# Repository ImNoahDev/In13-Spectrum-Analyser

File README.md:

# Nixie tube spectrum analyser

Warning: this is currently untested

I have designed an audio spectrum analyser that breaks an audio signal down into 7 frequency bands and displays each band on an in13 nixie tube. My project has Wifi allowing for smart home control. My project has a volume (changes sensitivity) and a brightness potentiometer. Each PCB takes a single audio signal input and 2 can be used for full stereo.

The case uses a laser cut kerf bend to allow the wrap around sheet to be cut in a single part. 

## Assembly instructions.

First manufacture and assemble the PCB according to the KiCad files. Next 3d print the top and bottom parts of the case. place the PCB onto the standoffs of the case with layer B (with the least components) facing upwards. Place the top of the case on and screw all part onto the standoffs. Laser cut the Wrap around and screw it in to the bottom mounting holes of the case while wrapping around the case to give a wooden front finish.

Code can be flashed through the USB port due to the built in USB-Serial converter.

## BOM

Note this is for 2x units (Left and Right) because most PCB manufacturers require at least 2 assembled and the price is not significantly more for 2 vs 1. This allows one per audio channel. The price of the tubes also wildly swings so I have put a placeholder value in that is roughly correct (depending on where you get them).

| Part name         | Cost    | Use                 | URL       |
| ----------------- | ------- | ------------------- | --------- |
| PCB Manufacture   | $11.20  | PCB                 | jlpcb.com |
| Economic PCBA     | $66.22  | Assemble PCB        | jlpcb.com |
| Components (PCBA) | $61.93  | Components for PCBA | jlpcb.com |
| Shipping          | $15     | PCB shipping        | jlpcb.com |
| In13 tubes        | $200    | Tubes               | Ebay      |
| Total:            | $343.35 |                     |           |

| Comment                     | Designator | Footprint                                  | Quantity |
| --------------------------- | ---------- | ------------------------------------------ | -------- |
| MJE340_                     | Q4         | TO126                                      | 1        |
| 10uF                        | C22        | C_1206_3216Metric                          | 1        |
| 4.7k                        | R38        | R_0603_1608Metric                          | 1        |
| 15k 1W                      | R14        | R_2512_6332Metric                          | 1        |
| 820k 0.25w 200v             | R44        | R_1206_3216Metric                          | 1        |
| 820 1/4w                    | R22        | R_1206_3216Metric                          | 1        |
| 0.1uF                       | C28        | C_0201_0603Metric                          | 1        |
| 10v 22uF                    | C5         | C_1206_3216Metric                          | 1        |
| 10uF                        | C11        | C_1206_3216Metric                          | 1        |
| 15k 1W                      | R34        | R_2512_6332Metric                          | 1        |
| USB_C_Receptacle_USB2.0_14P | J1         | USB_C_Receptacle_HCTL_HC-TYPE-C-16P-01A    | 1        |
| SW_Push                     | SW2        | 4312560387X6                               | 1        |
| MJE340_                     | Q2         | TO126                                      | 1        |
| 4.7k                        | R8         | R_0603_1608Metric                          | 1        |
| 0.05 1w                     | R43        | R_2512_6332Metric                          | 1        |
| 0.1uF                       | C15        | C_0603_1608Metric                          | 1        |
| ESP32-WROOM-32              | U3         | ESP32-WROOM-32                             | 1        |
| 15k 1W                      | R19        | R_2512_6332Metric                          | 1        |
| 2.2k 1/4W                   | R26        | R_1206_3216Metric                          | 1        |
| 0.1uF                       | C27        | C_0201_0603Metric                          | 1        |
| 0.1uF                       | C13        | C_0603_1608Metric                          | 1        |
| 2.2k 1/4W                   | R16        | R_1206_3216Metric                          | 1        |
| 2.2k 1/4W                   | R36        | R_1206_3216Metric                          | 1        |
| 10k                         | RV2        | Potentiometer_Alps_RK09K_Single_Horizontal | 1        |
| MSGEQ7                      | U2         | DIP-8_W7.62mm                              | 1        |
| 0.1uf                       | C25        | C_0201_0603Metric                          | 1        |
| SW_Push                     | SW3        | SW_SPST_SKQG_WithStem                      | 1        |
| 4.7k                        | R33        | R_0603_1608Metric                          | 1        |
| 820 1/4w                    | R37        | R_1206_3216Metric                          | 1        |
| MCP6002-xMC                 | U5         | DFN-8-1EP_3x2mm_P0.5mm_EP1.75x1.45mm       | 1        |
| 2.2k 1/4W                   | R31        | R_1206_3216Metric                          | 1        |
| IRFP250N                    | Q8         | TO-247-3_Horizontal_TabDown                | 1        |
| 56 uH                       | L1         | L_Ferrocore_DLG-0403                       | 1        |
| 10k                         | R46        | R_0603_1608Metric                          | 1        |
| 200K                        | R3         | R_0402_1005Metric                          | 1        |
| 4.7k                        | R18        | R_0603_1608Metric                          | 1        |
| 820 1/4w                    | R27        | R_1206_3216Metric                          | 1        |
| MJE340_                     | Q1         | TO126                                      | 1        |
| 0.1uF 10v                   | C10        | C_0402_1005Metric                          | 1        |
| 4.7k                        | R23        | R_0603_1608Metric                          | 1        |
| MJE340_                     | Q6         | TO126                                      | 1        |
| 4.7uF 10v                   | C1         | C_1206_3216Metric                          | 1        |
| 15k 1W                      | R24        | R_2512_6332Metric                          | 1        |
| 10K                         | R7         | R_0603_1608Metric                          | 1        |
| MJE340_                     | Q3         | TO126                                      | 1        |
| 0.1uF                       | C14        | C_0603_1608Metric                          | 1        |
| 0.1uF                       | C19        | C_0603_1608Metric                          | 1        |
| 0.1uF                       | C26        | C_0201_0603Metric                          | 1        |
| 100uF 16v                   | C21        | C_1206_3216Metric                          | 1        |
| 10V 1uF                     | C7         | C_1206_3216Metric                          | 1        |
| 10V 0.1uF                   | C4         | C_0402_1005Metric                          | 1        |
| MCP6002-xMC                 | U4         | DFN-8-1EP_3x2mm_P0.5mm_EP1.75x1.45mm       | 1        |
| 0.1uF                       | C17        | C_0603_1608Metric                          | 1        |
| 470k 1/4w                   | R40        | R_1206_3216Metric                          | 1        |
| 820 1/4w                    | R42        | R_1206_3216Metric                          | 1        |
| 0.1uF                       | C16        | C_0603_1608Metric                          | 1        |
| 10k 0.25w 200v              | R45        | R_1206_3216Metric                          | 1        |
| 15k 1W                      | R10        | R_2512_6332Metric                          | 1        |
| 470k 1/4w                   | R20        | R_1206_3216Metric                          | 1        |
| 47uF 200V                   | C23        | CP_Radial_D13.0mm_P5.00mm                  | 1        |
| SW_Push                     | SW1        | SW_SPST_SKQG_WithStem                      | 1        |
| RXD                         | TP2        | TestPoint_Pad_D1.0mm                       | 1        |
| 10K                         | R4         | R_0603_1608Metric                          | 1        |
| 5.1K                        | R1         | R_0402_1005Metric                          | 1        |
| 470k 1/4w                   | R25        | R_1206_3216Metric                          | 1        |
| 820 1/4w                    | R17        | R_1206_3216Metric                          | 1        |
| 470k 1/4w                   | R30        | R_1206_3216Metric                          | 1        |
| 10V 0.1uF                   | C6         | C_0402_1005Metric                          | 1        |
| 5.1K                        | R2         | R_0402_1005Metric                          | 1        |
| 470k 1/4w                   | R15        | R_1206_3216Metric                          | 1        |
| 0.1uF 10v                   | C9         | C_0402_1005Metric                          | 1        |
| 4.7k                        | R13        | R_0603_1608Metric                          | 1        |
| 10k                         | R47        | R_0603_1608Metric                          | 1        |
| TXD                         | TP1        | TestPoint_Pad_D1.0mm                       | 1        |
| 820 1/4w                    | R12        | R_1206_3216Metric                          | 1        |
| 4.7k                        | R28        | R_0603_1608Metric                          | 1        |
| 470k 1/4w                   | R9         | R_1206_3216Metric                          | 1        |
| 10k                         | RV3        | Potentiometer_Alps_RK09K_Single_Horizontal | 1        |
| MAX1771xSA                  | U11        | SO-8_3.9x4.9mm_P1.27mm                     | 1        |
| 2.2k 1/4W                   | R21        | R_1206_3216Metric                          | 1        |
| 18K                         | R5         | R_0603_1608Metric                          | 1        |
| 33k                         | R6         | R_0603_1608Metric                          | 1        |
| CH340C                      | U7         | SOIC-16_3.9x9.9mm_P1.27mm                  | 1        |
| MJE340_                     | Q5         | TO126                                      | 1        |
| UF4004                      | D2         | DIOAD1055W87L533D272                       | 1        |
| 0.1uF                       | C18        | C_0603_1608Metric                          | 1        |
| 10V 3.3uF                   | C3         | C_1206_3216Metric                          | 1        |
| 2.2k 1/4W                   | R41        | R_1206_3216Metric                          | 1        |
| 0.1uF                       | C12        | C_0603_1608Metric                          | 1        |
| 470k 1/4w                   | R35        | R_1206_3216Metric                          | 1        |
| MCP6002-xMC                 | U6         | DFN-8-1EP_3x2mm_P0.5mm_EP1.75x1.45mm       | 1        |
| 15k 1W                      | R39        | R_2512_6332Metric                          | 1        |
| AMS1117-3.3                 | U1         | SOT-223-3_TabPin2                          | 1        |
| 0.1uF 10v                   | C2         | C_0402_1005Metric                          | 1        |
| 15k 1W                      | R29        | R_2512_6332Metric                          | 1        |
| Conn_Coaxial                | J3         | RCA-Phono_CUI-Devices_RCJ-01X_Horizontal   | 1        |
| 0.1uF                       | C20        | C_0603_1608Metric                          | 1        |
| 33pF                        | C8         | C_0402_1005Metric                          | 1        |
| 0.1uF                       | C29        | C_0201_0603Metric                          | 1        |
| MJE340_                     | Q7         | TO126                                      | 1        |
| 0.1uF 250v                  | C24        | C_1206_3216Metric                          | 1        |
| 820 1/4w                    | R32        | R_1206_3216Metric                          | 1        |
| MCP6002-xMC                 | U18        | DFN-8-1EP_3x2mm_P0.5mm_EP1.75x1.45mm       | 1        |
| 2.2k 1/4W                   | R11        | R_1206_3216Metric                          | 1        |

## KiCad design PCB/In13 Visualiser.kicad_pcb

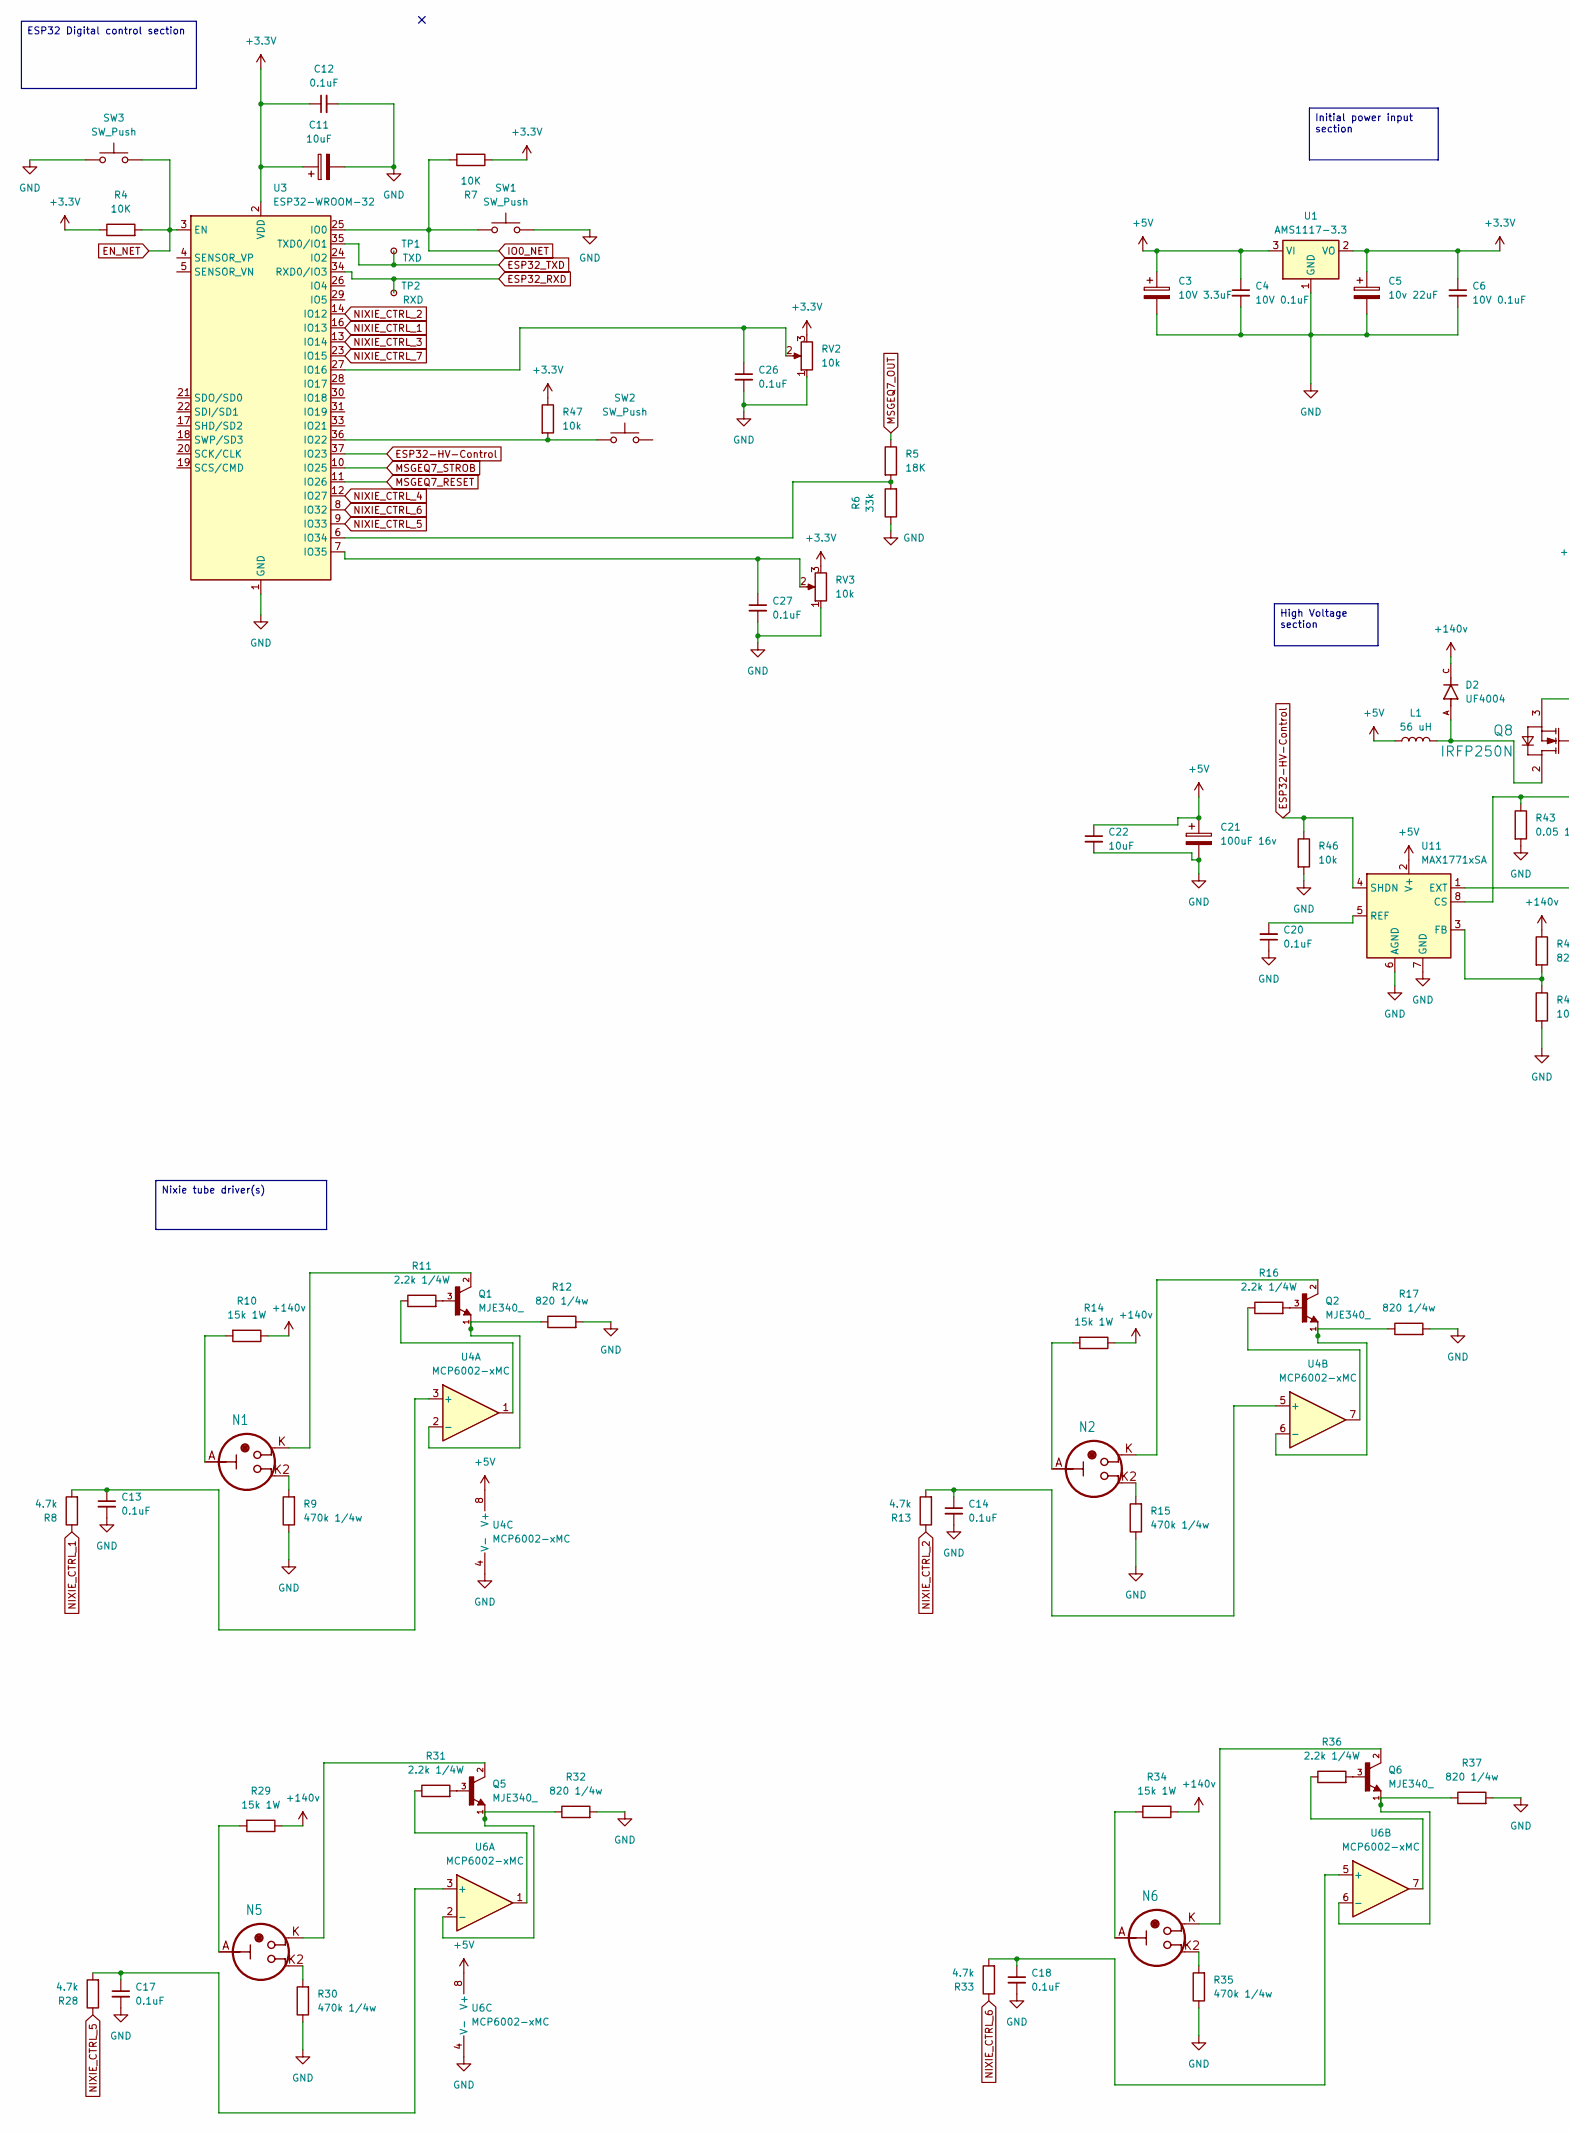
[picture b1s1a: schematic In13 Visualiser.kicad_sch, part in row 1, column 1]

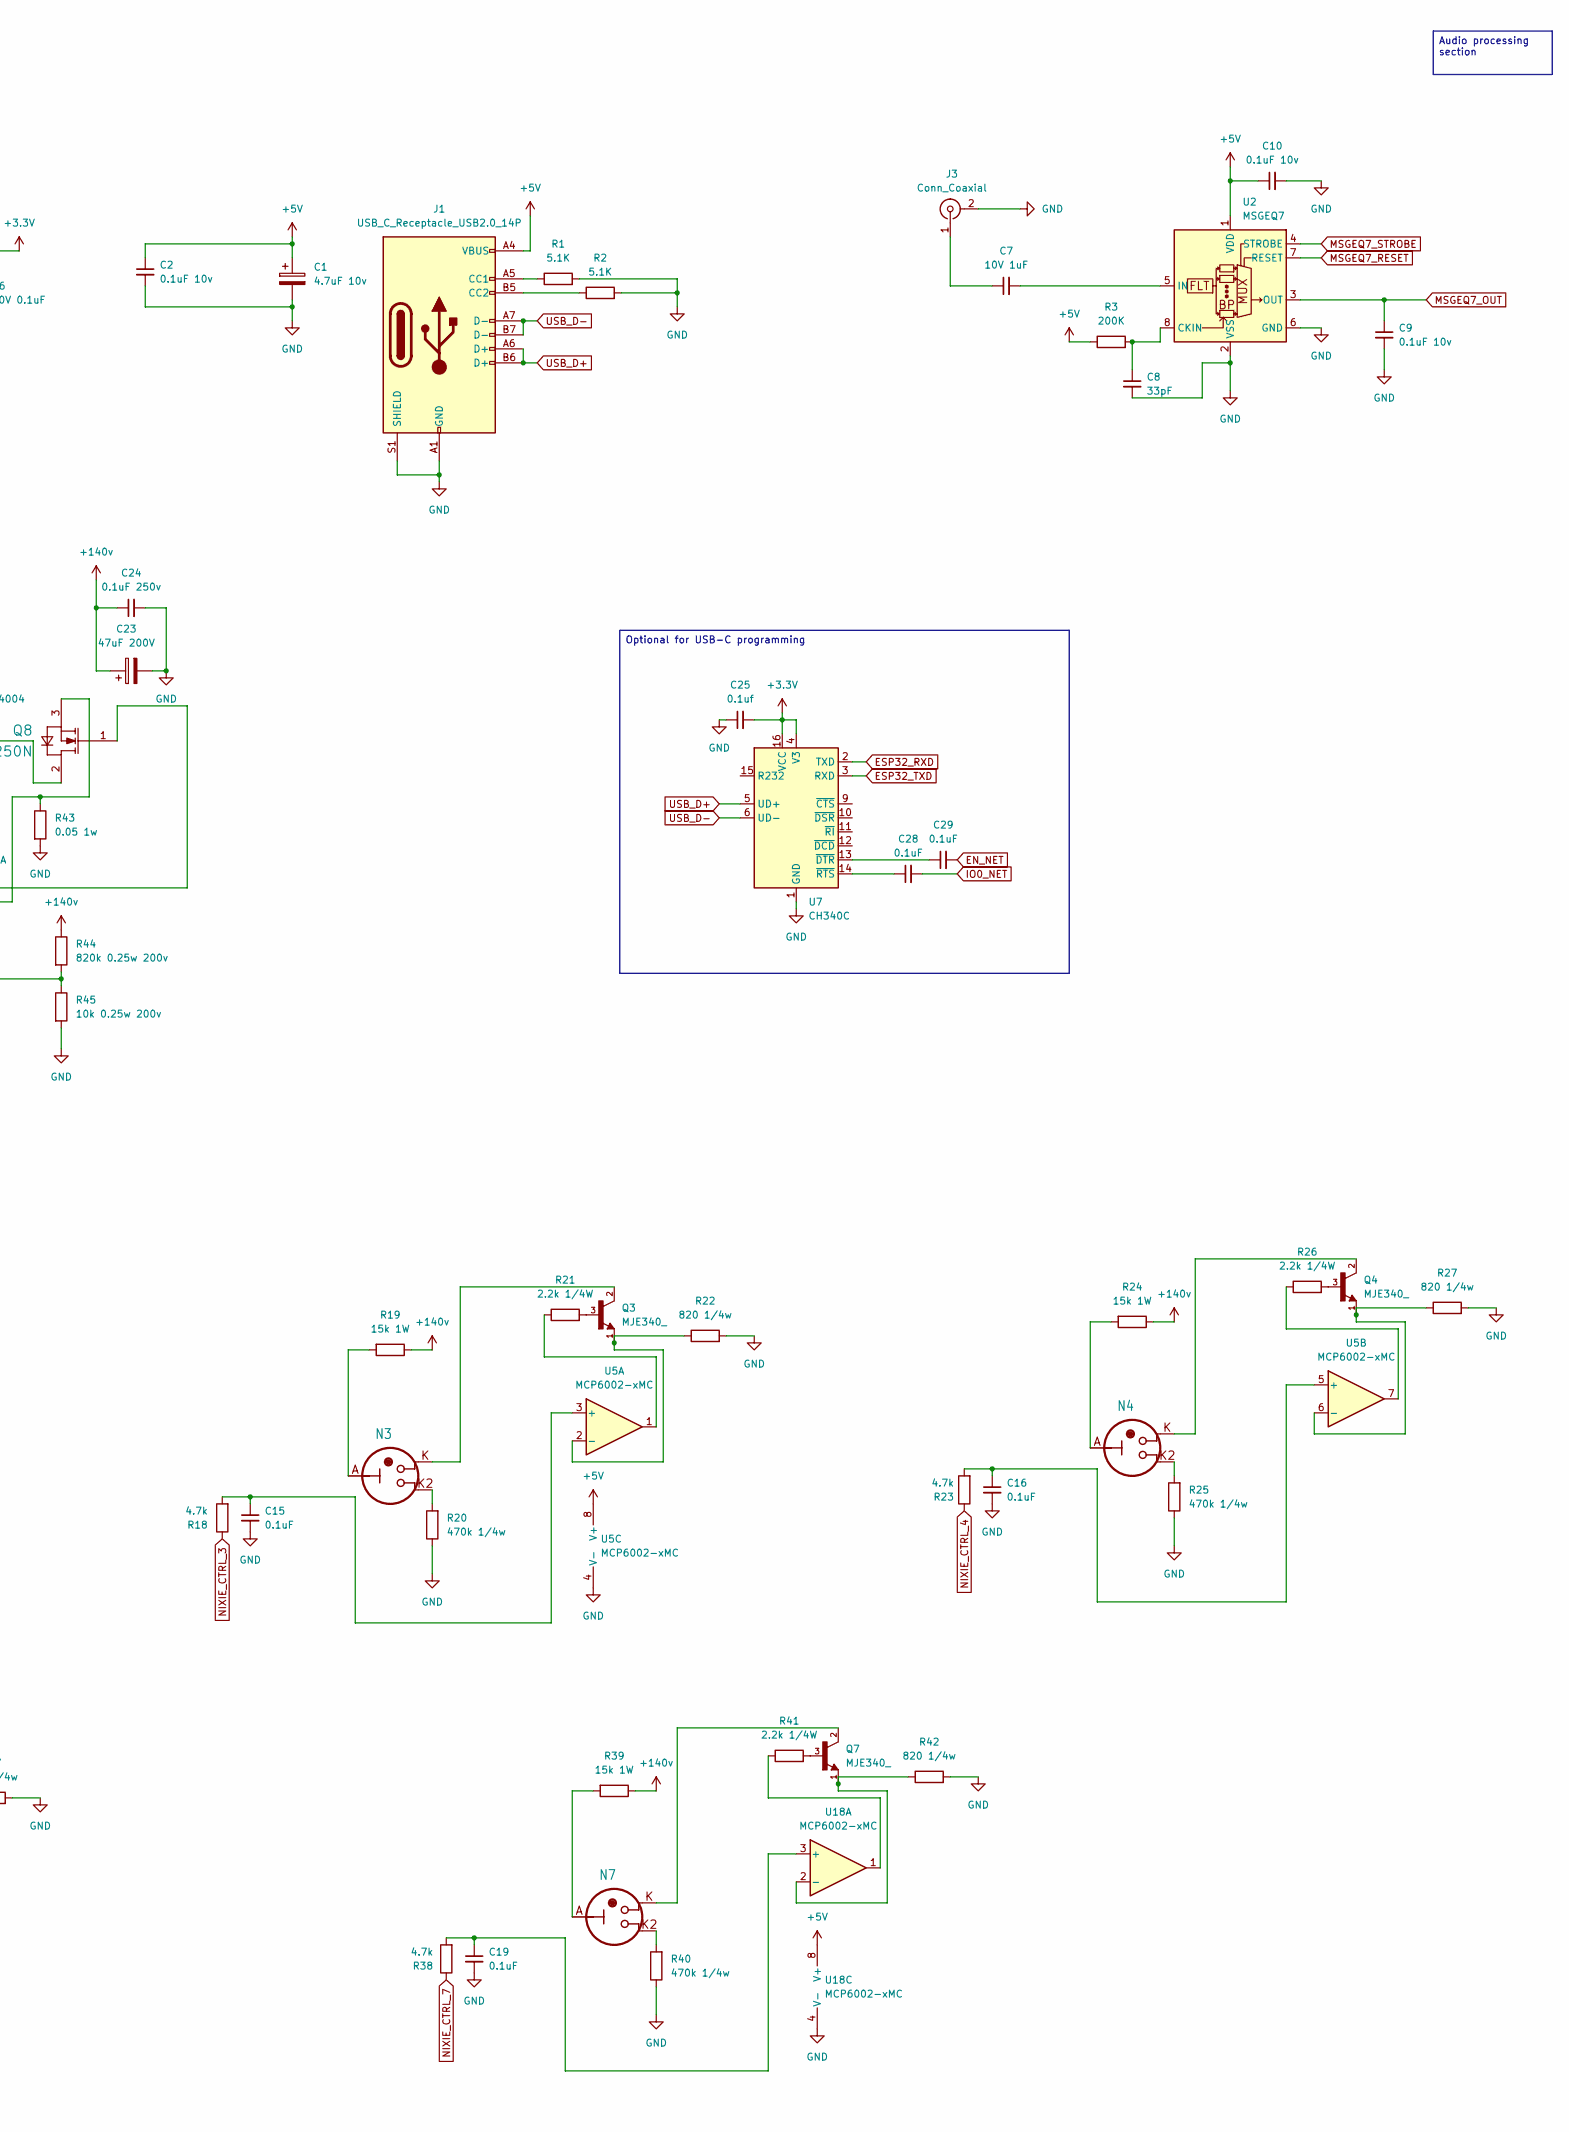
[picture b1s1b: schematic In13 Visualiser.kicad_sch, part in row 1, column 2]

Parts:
C1: 4.7uF 10v; C_1206_3216Metric
C2, C9, C10: 0.1uF 10v; C_0402_1005Metric
C3: 10V 3.3uF; C_1206_3216Metric
C4, C6: 10V 0.1uF; C_0402_1005Metric
C5: 10v 22uF; C_1206_3216Metric
C7: 10V 1uF; C_1206_3216Metric
C8: 33pF; C_0402_1005Metric
C11, C22: 10uF; C_1206_3216Metric
C12, C13, C14, C15, C16, C17, C18, C19, C20: 0.1uF; C_0603_1608Metric
C21: 100uF 16v; C_1206_3216Metric
C23: 47uF 200V; CP_Radial_D13.0mm_P5.00mm
C24: 0.1uF 250v; C_1206_3216Metric
C25: 0.1uf; C_0201_0603Metric
C26, C27, C28, C29: 0.1uF; C_0201_0603Metric
D2: UF4004; DIOAD1055W87L533D272; PARTREV N/A
J1: USB_C_Receptacle_USB2.0_14P; USB_C_Receptacle_HCTL_HC-TYPE-C-16P-01A
J3: Conn_Coaxial; RCA-Phono_CUI-Devices_RCJ-01X_Horizontal
L1: 56 uH; L_Ferrocore_DLG-0403
N1, N2, N3, N4, N5, N6, N7: nixies-us-IN-13
Q1, Q2, Q3, Q4, Q5, Q6, Q7: MJE340_; TO126
Q8: IRFP250N; TO-247-3_Horizontal_TabDown
R1, R2: 5.1K; R_0402_1005Metric
R3: 200K; R_0402_1005Metric
R4, R7: 10K; R_0603_1608Metric
R5: 18K; R_0603_1608Metric
R6: 33k; R_0603_1608Metric
R8, R13, R18, R23, R28, R33, R38: 4.7k; R_0603_1608Metric
R9, R15, R20, R25, R30, R35, R40: 470k 1/4w; R_1206_3216Metric
R10, R14, R19, R24, R29, R34, R39: 15k 1W; R_2512_6332Metric
R11, R16, R21, R26, R31, R36, R41: 2.2k 1/4W; R_1206_3216Metric
R12, R17, R22, R27, R32, R37, R42: 820 1/4w; R_1206_3216Metric
R43: 0.05 1w; R_2512_6332Metric
R44: 820k 0.25w 200v; R_1206_3216Metric
R45: 10k 0.25w 200v; R_1206_3216Metric
R46, R47: 10k; R_0603_1608Metric
RV2, RV3: 10k; Potentiometer_Alps_RK09K_Single_Horizontal
SW1, SW3: SW_Push; SW_SPST_SKQG_WithStem
SW2: SW_Push; 4312560387X6
TP1: TXD; TestPoint_Pad_D1.0mm
TP2: RXD; TestPoint_Pad_D1.0mm
U1: AMS1117-3.3; SOT-223-3_TabPin2
U2: MSGEQ7; DIP-8_W7.62mm
U3: ESP32-WROOM-32
U4, U5, U6, U18: MCP6002-xMC; DFN-8-1EP_3x2mm_P0.5mm_EP1.75x1.45mm
U7: CH340C; SOIC-16_3.9x9.9mm_P1.27mm
U11: MAX1771xSA; SO-8_3.9x4.9mm_P1.27mm

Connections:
+3.3V: C5.1, C6.1, C11.1, C12.1, C25.2, R4.1, R7.1, R47.1, RV2.3, RV3.3, U1.2 (VO), U3.2 (VDD), U7.4 (V3), U7.16 (VCC)
+5V: C1.1, C2.1, C3.1, C4.1, C10.1, C21.1, C22.1, J1.A4 (VBUS), J1.A9 (VBUS), J1.B4 (VBUS), J1.B9 (VBUS), L1.1, R3.1, U1.3 (VI), U2.1 (VDD), U4.8 (V+), U5.8 (V+), U6.8 (V+), U11.2 (V+), U18.8 (V+)
+140v: C23.1, C24.1, D2.C, R10.1, R14.1, R19.1, R24.1, R29.1, R34.1, R39.1, R44.1
EN_NET: C29.2, R4.2, SW3.2, U3.3 (EN)
ESP32-HV-Control: R46.1, U3.37 (IO23), U11.4 (SHDN)
ESP32_RXD: TP2.1, U3.34 (RXD0/IO3), U7.2 (TXD)
ESP32_TXD: TP1.1, U3.35 (TXD0/IO1), U7.3 (RXD)
GND: C1.2, C2.2, C3.2, C4.2, C5.2, C6.2, C8.2, C9.2, C10.2, C11.2, C12.2, C13.2, C14.2, C15.2, C16.2, C17.2, C18.2, C19.2, C20.1, C21.2, C22.2, C23.2, C24.2, C25.1, C26.2, C27.2, J1.A1 (GND), J1.A12 (GND), J1.B1 (GND), J1.B12 (GND), J1.S1 (SHIELD), J3.2 (Ext), R1.2, R2.2, R6.1, R9.1, R12.2, R15.1, R17.2, R20.1, R22.2, R25.1, R27.2, R30.1, R32.2, R35.1, R37.2, R40.1, R42.2, R43.2, R45.2, R46.2, RV2.1, RV3.1, SW1.2, SW3.1, U1.1 (GND), U2.2 (VSS), U2.6 (GND), U3.1 (GND), U3.15 (GND), U3.38 (GND), U3.39 (GND), U4.4 (V-), U4.9 (V-), U5.4 (V-), U5.9 (V-), U6.4 (V-), U6.9 (V-), U7.1 (GND), U11.6 (AGND), U11.7 (GND), U18.4 (V-), U18.9 (V-)
IO0_NET: C28.2, R7.2, SW1.1, U3.25 (IO0)
MSGEQ7_OUT: C9.1, R5.1, U2.3 (OUT)
MSGEQ7_RESET: U2.7 (RESET), U3.11 (IO26)
MSGEQ7_STROB: U3.10 (IO25)
MSGEQ7_STROBE: U2.4 (STROBE)
NIXIE_CTRL_1: R8.1, U3.16 (IO13)
NIXIE_CTRL_2: R13.1, U3.14 (IO12)
NIXIE_CTRL_3: R18.1, U3.13 (IO14)
NIXIE_CTRL_4: R23.1, U3.12 (IO27)
NIXIE_CTRL_5: R28.1, U3.9 (IO33)
NIXIE_CTRL_6: R33.1, U3.8 (IO32)
NIXIE_CTRL_7: R38.1, U3.23 (IO15)
unnamed: J1.A5 (CC1), R1.1
unnamed: J1.B5 (CC2), R2.1
unnamed: C7.1, J3.1 (In)
unnamed: N1.A, R10.2
unnamed: N1.K2, R9.2
unnamed: N1.K, Q1.2
unnamed: N2.A, R14.2
unnamed: N2.K2, R15.2
unnamed: N2.K, Q2.2
unnamed: N3.A, R19.2
unnamed: N3.K2, R20.2
unnamed: N3.K, Q3.2
unnamed: N4.A, R24.2
unnamed: N4.K2, R25.2
unnamed: N4.K, Q4.2
unnamed: N5.A, R29.2
unnamed: N5.K2, R30.2
unnamed: N5.K, Q5.2
unnamed: N6.A, R34.2
unnamed: N6.K2, R35.2
unnamed: N6.K, Q6.2
unnamed: N7.A, R39.2
unnamed: N7.K2, R40.2
unnamed: N7.K, Q7.2
unnamed: Q1.3, R11.2
unnamed: Q2.3, R16.2
unnamed: Q3.3, R21.2
unnamed: Q4.3, R26.2
unnamed: Q5.3, R31.2
unnamed: Q6.3, R36.2
unnamed: Q7.3, R41.2
unnamed: D2.A, L1.2, Q8.2 (DRAIN)
unnamed: Q8.1 (GATE), U11.1 (EXT)
unnamed: Q8.3 (SOURCE), R43.1, U11.8 (CS)
unnamed: R11.1, U4.1
unnamed: R16.1, U4.7
unnamed: R21.1, U5.1
unnamed: R26.1, U5.7
unnamed: R31.1, U6.1
unnamed: R36.1, U6.7
unnamed: R41.1, U18.1
unnamed: C8.1, R3.2, U2.8 (CKIN)
unnamed: C7.2, U2.5 (IN)
unnamed: C26.1, RV2.2, U3.27 (IO16)
unnamed: R47.2, SW2.1, U3.36 (IO22)
unnamed: R5.2, R6.2, U3.6 (IO34)
unnamed: C27.1, RV3.2, U3.7 (IO35)
unnamed: C13.1, R8.2, U4.3 (+)
unnamed: Q1.1, R12.1, U4.2 (-)
unnamed: C14.1, R13.2, U4.5 (+)
unnamed: Q2.1, R17.1, U4.6 (-)
unnamed: C15.1, R18.2, U5.3 (+)
unnamed: Q3.1, R22.1, U5.2 (-)
unnamed: C16.1, R23.2, U5.5 (+)
unnamed: Q4.1, R27.1, U5.6 (-)
unnamed: C17.1, R28.2, U6.3 (+)
unnamed: Q5.1, R32.1, U6.2 (-)
unnamed: C18.1, R33.2, U6.5 (+)
unnamed: Q6.1, R37.1, U6.6 (-)
unnamed: C29.1, U7.13 (~DTR)
unnamed: C28.1, U7.14 (~RTS)
unnamed: R44.2, R45.1, U11.3 (FB)
unnamed: C20.2, U11.5 (REF)
unnamed: C19.1, R38.2, U18.3 (+)
unnamed: Q7.1, R42.1, U18.2 (-)
USB_D+: J1.A6 (D+), J1.B6 (D+), U7.5 (UD+)
USB_D-: J1.A7 (D-), J1.B7 (D-), U7.6 (UD-)

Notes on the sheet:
Initial power input section
High Voltage section
Nixie tube driver(s)
ESP32 Digital control section
Audio processing section
Optional for USB-C programming

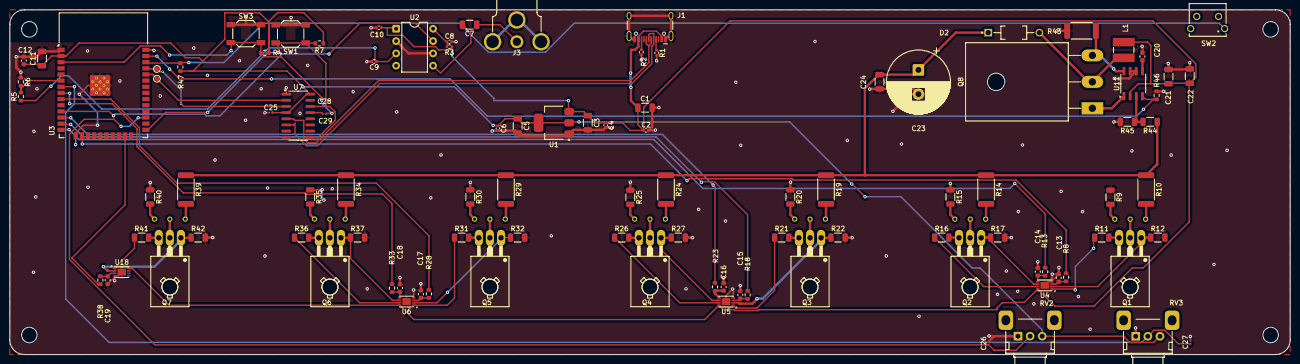
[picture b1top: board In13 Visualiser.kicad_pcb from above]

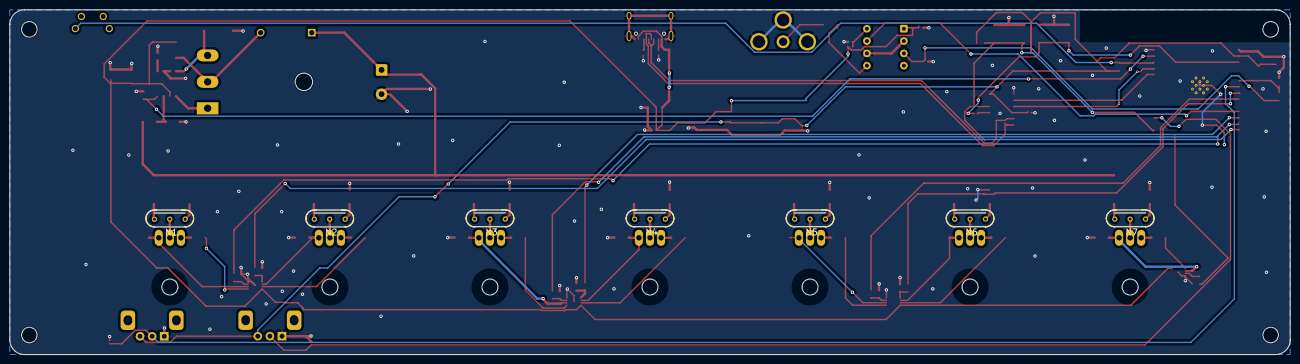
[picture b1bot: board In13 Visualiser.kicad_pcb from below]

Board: 2 copper layers, 264.2 x 71.1 mm, 115 parts (7 on the bottom side), 85 nets.

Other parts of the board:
Hole1, Hole2, Hole3, Hole4: MountingHole_3.2mm_M3

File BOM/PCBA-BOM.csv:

Comment,Designator,Footprint,LCSC,Quantity
MJE340_,Q4,TO126,,1
10uF,C22,C_1206_3216Metric,,1
4.7k,R38,R_0603_1608Metric,,1
15k 1W,R14,R_2512_6332Metric,,1
820k 0.25w 200v,R44,R_1206_3216Metric,,1
820 1/4w,R22,R_1206_3216Metric,,1
0.1uF,C28,C_0201_0603Metric,,1
10v 22uF,C5,C_1206_3216Metric,,1
10uF,C11,C_1206_3216Metric,,1
15k 1W,R34,R_2512_6332Metric,,1
USB_C_Receptacle_USB2.0_14P,J1,USB_C_Receptacle_HCTL_HC-TYPE-C-16P-01A,,1
SW_Push,SW2,4312560387X6,,1
MJE340_,Q2,TO126,,1
4.7k,R8,R_0603_1608Metric,,1
0.05 1w,R43,R_2512_6332Metric,,1
0.1uF,C15,C_0603_1608Metric,,1
ESP32-WROOM-32,U3,ESP32-WROOM-32,,1
15k 1W,R19,R_2512_6332Metric,,1
2.2k 1/4W,R26,R_1206_3216Metric,,1
0.1uF,C27,C_0201_0603Metric,,1
0.1uF,C13,C_0603_1608Metric,,1
2.2k 1/4W,R16,R_1206_3216Metric,,1
2.2k 1/4W,R36,R_1206_3216Metric,,1
10k,RV2,Potentiometer_Alps_RK09K_Single_Horizontal,,1
MSGEQ7,U2,DIP-8_W7.62mm,,1
0.1uf,C25,C_0201_0603Metric,,1
SW_Push,SW3,SW_SPST_SKQG_WithStem,,1
4.7k,R33,R_0603_1608Metric,,1
820 1/4w,R37,R_1206_3216Metric,,1
MCP6002-xMC,U5,DFN-8-1EP_3x2mm_P0.5mm_EP1.75x1.45mm,,1
2.2k 1/4W,R31,R_1206_3216Metric,,1
IRFP250N,Q8,TO-247-3_Horizontal_TabDown,,1
56 uH,L1,L_Ferrocore_DLG-0403,,1
10k,R46,R_0603_1608Metric,,1
200K,R3,R_0402_1005Metric,,1
4.7k,R18,R_0603_1608Metric,,1
820 1/4w,R27,R_1206_3216Metric,,1
MJE340_,Q1,TO126,,1
0.1uF 10v,C10,C_0402_1005Metric,,1
4.7k,R23,R_0603_1608Metric,,1
MJE340_,Q6,TO126,,1
4.7uF 10v,C1,C_1206_3216Metric,,1
15k 1W,R24,R_2512_6332Metric,,1
10K,R7,R_0603_1608Metric,,1
MJE340_,Q3,TO126,,1
0.1uF,C14,C_0603_1608Metric,,1
0.1uF,C19,C_0603_1608Metric,,1
0.1uF,C26,C_0201_0603Metric,,1
100uF 16v,C21,C_1206_3216Metric,,1
10V 1uF,C7,C_1206_3216Metric,,1
10V 0.1uF,C4,C_0402_1005Metric,,1
MCP6002-xMC,U4,DFN-8-1EP_3x2mm_P0.5mm_EP1.75x1.45mm,,1
0.1uF,C17,C_0603_1608Metric,,1
470k 1/4w,R40,R_1206_3216Metric,,1
820 1/4w,R42,R_1206_3216Metric,,1
0.1uF,C16,C_0603_1608Metric,,1
10k 0.25w 200v,R45,R_1206_3216Metric,,1
15k 1W,R10,R_2512_6332Metric,,1
470k 1/4w,R20,R_1206_3216Metric,,1
47uF 200V,C23,CP_Radial_D13.0mm_P5.00mm,,1
SW_Push,SW1,SW_SPST_SKQG_WithStem,,1
RXD,TP2,TestPoint_Pad_D1.0mm,,1
10K,R4,R_0603_1608Metric,,1
5.1K,R1,R_0402_1005Metric,,1
470k 1/4w,R25,R_1206_3216Metric,,1
820 1/4w,R17,R_1206_3216Metric,,1
470k 1/4w,R30,R_1206_3216Metric,,1
10V 0.1uF,C6,C_0402_1005Metric,,1
5.1K,R2,R_0402_1005Metric,,1
470k 1/4w,R15,R_1206_3216Metric,,1
0.1uF 10v,C9,C_0402_1005Metric,,1
4.7k,R13,R_0603_1608Metric,,1
10k,R47,R_0603_1608Metric,,1
TXD,TP1,TestPoint_Pad_D1.0mm,,1
820 1/4w,R12,R_1206_3216Metric,,1
4.7k,R28,R_0603_1608Metric,,1
470k 1/4w,R9,R_1206_3216Metric,,1
10k,RV3,Potentiometer_Alps_RK09K_Single_Horizontal,,1
MAX1771xSA,U11,SO-8_3.9x4.9mm_P1.27mm,,1
2.2k 1/4W,R21,R_1206_3216Metric,,1
18K,R5,R_0603_1608Metric,,1
33k,R6,R_0603_1608Metric,,1
CH340C,U7,SOIC-16_3.9x9.9mm_P1.27mm,,1
MJE340_,Q5,TO126,,1
UF4004,D2,DIOAD1055W87L533D272,,1
0.1uF,C18,C_0603_1608Metric,,1
10V 3.3uF,C3,C_1206_3216Metric,,1
2.2k 1/4W,R41,R_1206_3216Metric,,1
0.1uF,C12,C_0603_1608Metric,,1
470k 1/4w,R35,R_1206_3216Metric,,1
MCP6002-xMC,U6,DFN-8-1EP_3x2mm_P0.5mm_EP1.75x1.45mm,,1
15k 1W,R39,R_2512_6332Metric,,1
AMS1117-3.3,U1,SOT-223-3_TabPin2,,1
0.1uF 10v,C2,C_0402_1005Metric,,1
15k 1W,R29,R_2512_6332Metric,,1
Conn_Coaxial,J3,RCA-Phono_CUI-Devices_RCJ-01X_Horizontal,,1
0.1uF,C20,C_0603_1608Metric,,1
33pF,C8,C_0402_1005Metric,,1
0.1uF,C29,C_0201_0603Metric,,1
MJE340_,Q7,TO126,,1
0.1uF 250v,C24,C_1206_3216Metric,,1
820 1/4w,R32,R_1206_3216Metric,,1
MCP6002-xMC,U18,DFN-8-1EP_3x2mm_P0.5mm_EP1.75x1.45mm,,1
2.2k 1/4W,R11,R_1206_3216Metric,,1
~,N7,nixies-us-IN-13,,1
~,N3,nixies-us-IN-13,,1
~,N1,nixies-us-IN-13,,1
~,N6,nixies-us-IN-13,,1
~,N5,nixies-us-IN-13,,1
~,N4,nixies-us-IN-13,,1
~,N2,nixies-us-IN-13,,1

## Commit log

2025-05-18 Init
2025-05-18 Power input
2025-05-18 image.png
2025-05-19 Audio
2025-05-19 ESP32
2025-05-19 Nixie driver
2025-05-20 Boost supply
2025-05-21 routing iteration 1
2025-05-21 hours
2025-05-22 PCB 2
2025-05-28 Add case
2025-05-28 re-route
2025-06-01 add files
2025-06-01 update render
2025-06-02 repo.png
2025-08-08 Implement ESP32 spectrum analyzer with WiFi, calibration, and web UI
2025-08-08 Remove brightness control and related functionality
2025-08-08 Implement dual-core audio processing with FreeRTOS task
2025-08-08 Update pin assignments and add spare potentiometer input
2025-08-08 Add beat pulse feature to drive external effects via IO16
2025-08-08 Remove beat pulse feature and related code
2026-03-15 Add warning about untested project
    Added a warning about the project being untested.
